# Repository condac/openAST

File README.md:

NEW! Arduino code
=================

I strongly recomend switching to the arduino based code. All future changes will be made here. It is much more easy to work with now that I have managed to get the critical timings right to send a correct signal. 

To add support for attiny in Arduino follow this guide https://create.arduino.cc/projecthub/arjun/programming-attiny85-with-arduino-uno-afb829

Do note that if you try to program your attiny mounted in the transponder you need to desolder the resistor on the antenna loop or the device will not respond correctly ( giving wrong board id errors and not responding well at all etc...) And you still need to supply the chip with an own oscilator source because it do not like to use the 20mhz crystal in programming mode for some reason.

openAST
=======

open source Axx Simulated transponder

This is for an attiny25 running at 20MHz

set fuse to -U lfuse:w:0xff:m in avrdude

To use the java program to encode run:

    cd encoderProgram/java/dist
    java -jar rctcode.jar 3456789

    encode2: 0101001000010111011001000101010000000000
    encodeOut:  1110000111001011111111010010100100101000000100110001110100010011001111110000
        ldi  d1,  0xe1
        ldi  d2,  0xcb
        ldi  d3,  0xfd
        ldi  d4,  0x29
        ldi  d5,  0x28
        ldi  d6,  0x13
        ldi  d7,  0x1d
        ldi  d8,  0x13
        ldi  d9,  0x3f
And the last lines you can paste in the asm file when you build your program and you have it ready to go. 

To decode, input a binary string as argument (at least 12 char) 

    java -jar rctcode.jar 1110000111001011111111010010100100101000000100110001110100010011001111110000
      known decoded: 01010010000101110110010001010100000000
      known decoded int: 3456789

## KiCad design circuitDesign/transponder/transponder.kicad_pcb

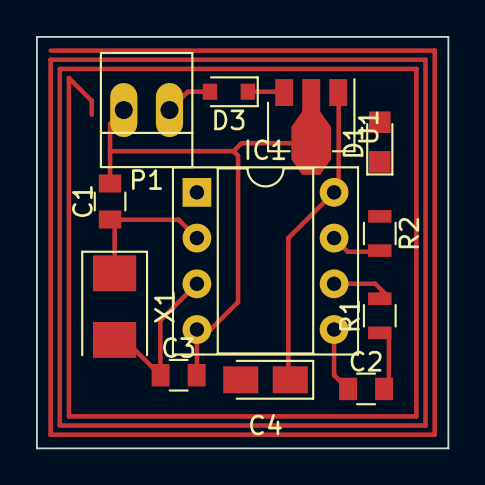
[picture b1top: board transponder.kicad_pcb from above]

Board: 2 copper layers, 22.9 x 22.9 mm, 12 parts (0 on the bottom side), 11 nets.

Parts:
C1, C3: 22pF; C_0805
C2: 1nF; C_0805
C4: 50uF; CP_Tantalum_Case-A_EIA-3216-18_Reflow
D1: LED; LED_0805
D3: DIODE; D_0805
IC1: ATTINY85-P; DIP-8_W7.62mm_Socket
P1: CONN_2; PINHEAD1-2
R1: 220; R_0805
R2: 1k; R_0805
U1: L78L05_SOT89; SOT-89-3
X1: CRYSTAL; Crystal_SMD_5032-2pin_5.0x3.2mm

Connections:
GND: C1.2, C3.2, C4.2, IC1.4, P1.2, U1.2
unnamed: C1.1, IC1.2, X1.1
unnamed: C2.1, IC1.5
unnamed: C2.2, R1.1
unnamed: C3.1, IC1.3, X1.2
unnamed: C4.1, D1.2, IC1.8, U1.1
unnamed: D1.1, R2.1
unnamed: D3.1, U1.3
unnamed: D3.2, P1.1
unnamed: IC1.6, R1.2
unnamed: IC1.7, R2.2

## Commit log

2014-07-25 Update README.md
    don't know if the name mentioned was trademarked so i removed it
2014-08-01 initial commit, working with old decoders
2014-08-01 added license
2014-08-01 Added KiCAD schematics for hardware
2014-08-01 Added diode values
2014-08-02 added encode and decode program in C and Java
2014-08-02 fixed input arguments for Java program
2015-08-18 update circuit
2018-05-02 Added Arduino version of code
2018-05-03 Functions for status messages
2018-05-03 python program
2018-05-03 fixed ghost output
2018-05-04 Working encoderprogram for python
2018-05-10 First working arduino version
2018-05-14 Updated blackbox with working and tested design
2018-05-24 PCB work, and more
2018-05-24 PCB print version
2018-05-25 fixed pcb text on soldermasks
2018-05-25 4x4 array for pcb printing
2018-06-21 Defines for delay
2021-04-12 Fix so transponder is using same phase every time
2021-04-21 ctc test
